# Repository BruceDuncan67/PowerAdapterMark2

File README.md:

# PowerAdapterMark2
newest version of power adapter board using global libraries

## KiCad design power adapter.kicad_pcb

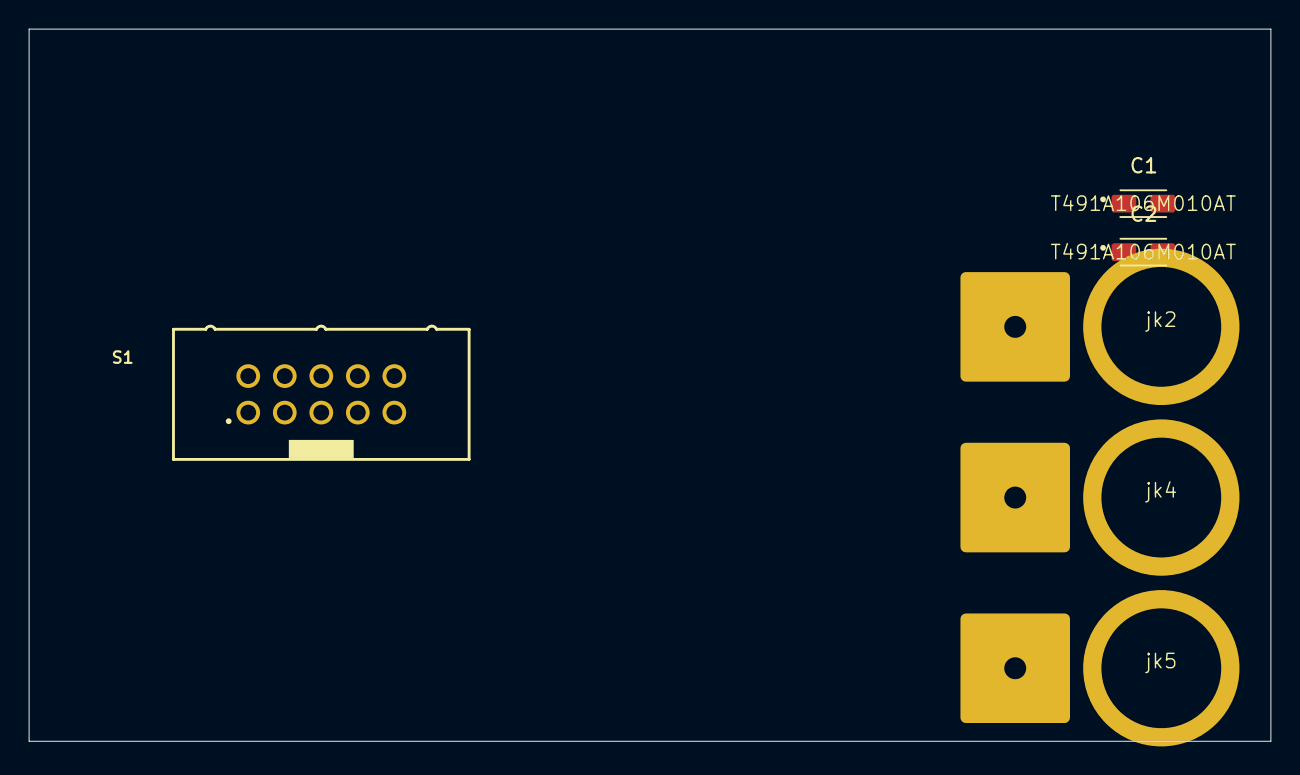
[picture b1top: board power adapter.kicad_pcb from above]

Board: 2 copper layers, 86.4 x 49.5 mm, 6 parts (0 on the bottom side), 3 nets, no tracks yet.

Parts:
C1, C2: T491A106M010AT; CAPPM3216X180N
S1: 2x5header
jk2, jk4, jk5: Banana

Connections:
+12V: C1.1, S1.2, jk2.2
-12V: C2.2, S1.9, S1.10, jk4.2
GND: C1.2, C2.1, S1.3, S1.4, S1.5, S1.6, S1.7, S1.8, jk5.2

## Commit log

2025-11-08 Add files via upload
    firstcommit
2025-11-08 added caps to power header
2025-11-09 added global lib repo to preferences
2025-11-09 added my golden test resistor and updated symbol and footprint directories in paths
